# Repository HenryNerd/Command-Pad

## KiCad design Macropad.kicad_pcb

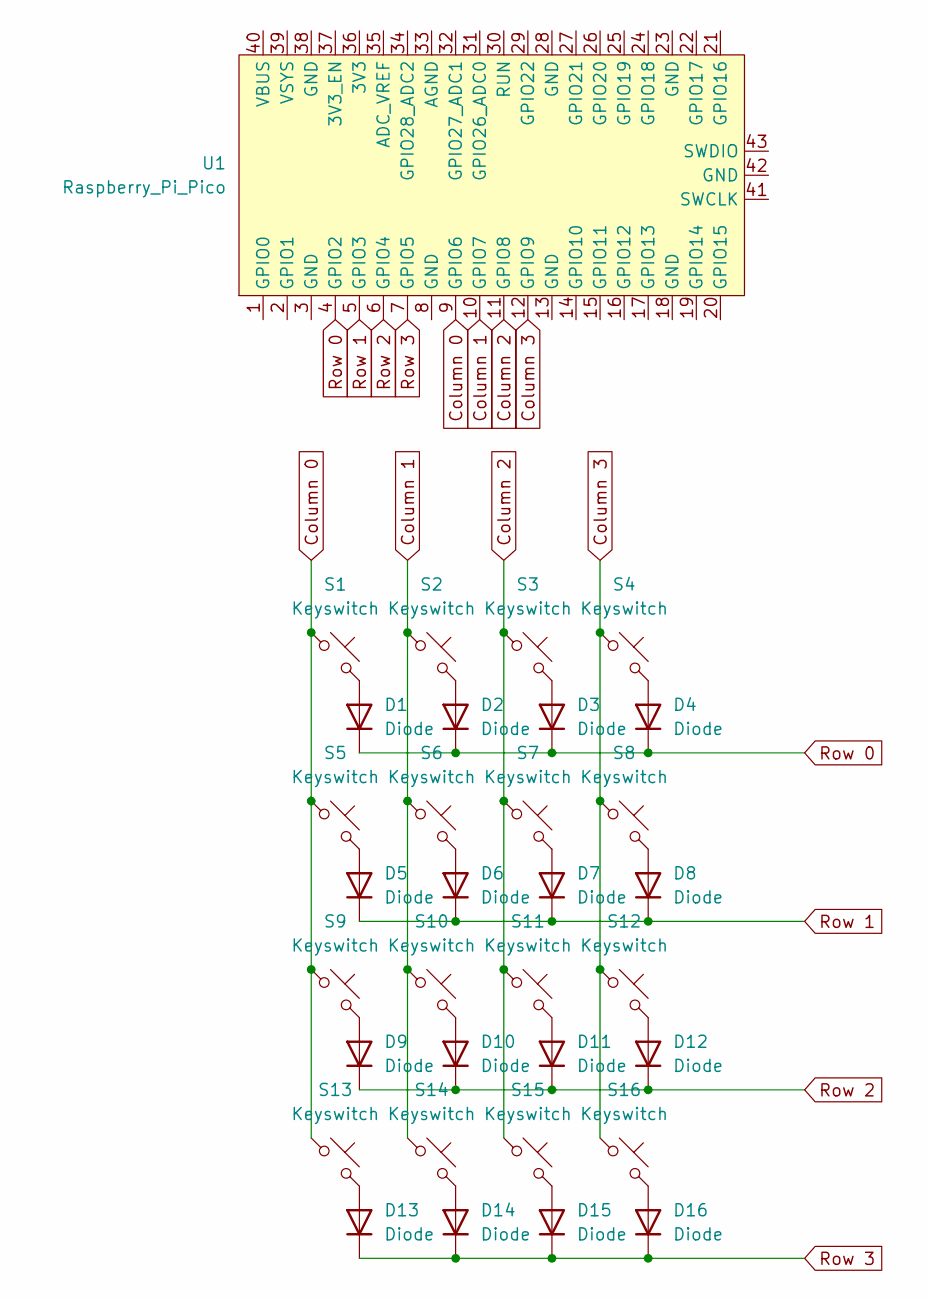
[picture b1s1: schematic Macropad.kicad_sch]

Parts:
D1, D2, D3, D4, D5, D6, D7, D8, D9, D10, D11, D12, D13, D14, D15, D16: Diode
S1, S2, S3, S4, S5, S6, S7, S8, S9, S10, S11, S12, S13, S14, S15, S16: Keyswitch
U1: Raspberry_Pi_Pico

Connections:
Column 0: S1.1, S5.1, S9.1, S13.1, U1.9 (GPIO6)
Column 1: S2.1, S6.1, S10.1, S14.1, U1.10 (GPIO7)
Column 2: S3.1, S7.1, S11.1, S15.1, U1.11 (GPIO8)
Column 3: S4.1, S8.1, S12.1, S16.1, U1.12 (GPIO9)
unnamed: D1.2 (A), S1.2
unnamed: D2.2 (A), S2.2
unnamed: D3.2 (A), S3.2
unnamed: D4.2 (A), S4.2
unnamed: D5.2 (A), S5.2
unnamed: D6.2 (A), S6.2
unnamed: D7.2 (A), S7.2
unnamed: D8.2 (A), S8.2
unnamed: D9.2 (A), S9.2
unnamed: D10.2 (A), S10.2
unnamed: D11.2 (A), S11.2
unnamed: D12.2 (A), S12.2
unnamed: D13.2 (A), S13.2
unnamed: D14.2 (A), S14.2
unnamed: D15.2 (A), S15.2
unnamed: D16.2 (A), S16.2
Row 0: D1.1 (K), D2.1 (K), D3.1 (K), D4.1 (K), U1.4 (GPIO2)
Row 1: D5.1 (K), D6.1 (K), D7.1 (K), D8.1 (K), U1.5 (GPIO3)
Row 2: D9.1 (K), D10.1 (K), D11.1 (K), D12.1 (K), U1.6 (GPIO4)
Row 3: D13.1 (K), D14.1 (K), D15.1 (K), D16.1 (K), U1.7 (GPIO5)

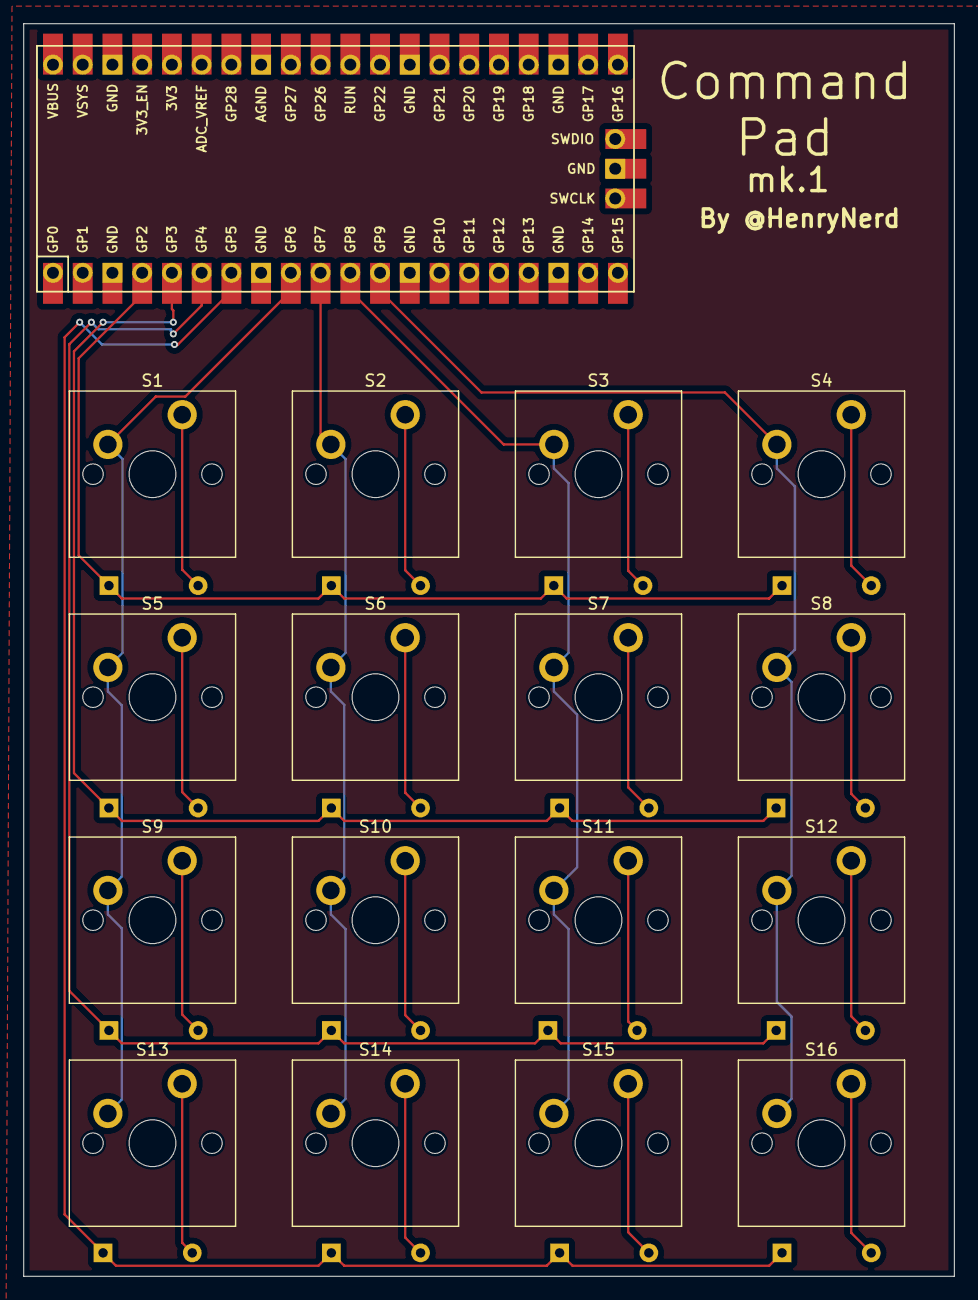
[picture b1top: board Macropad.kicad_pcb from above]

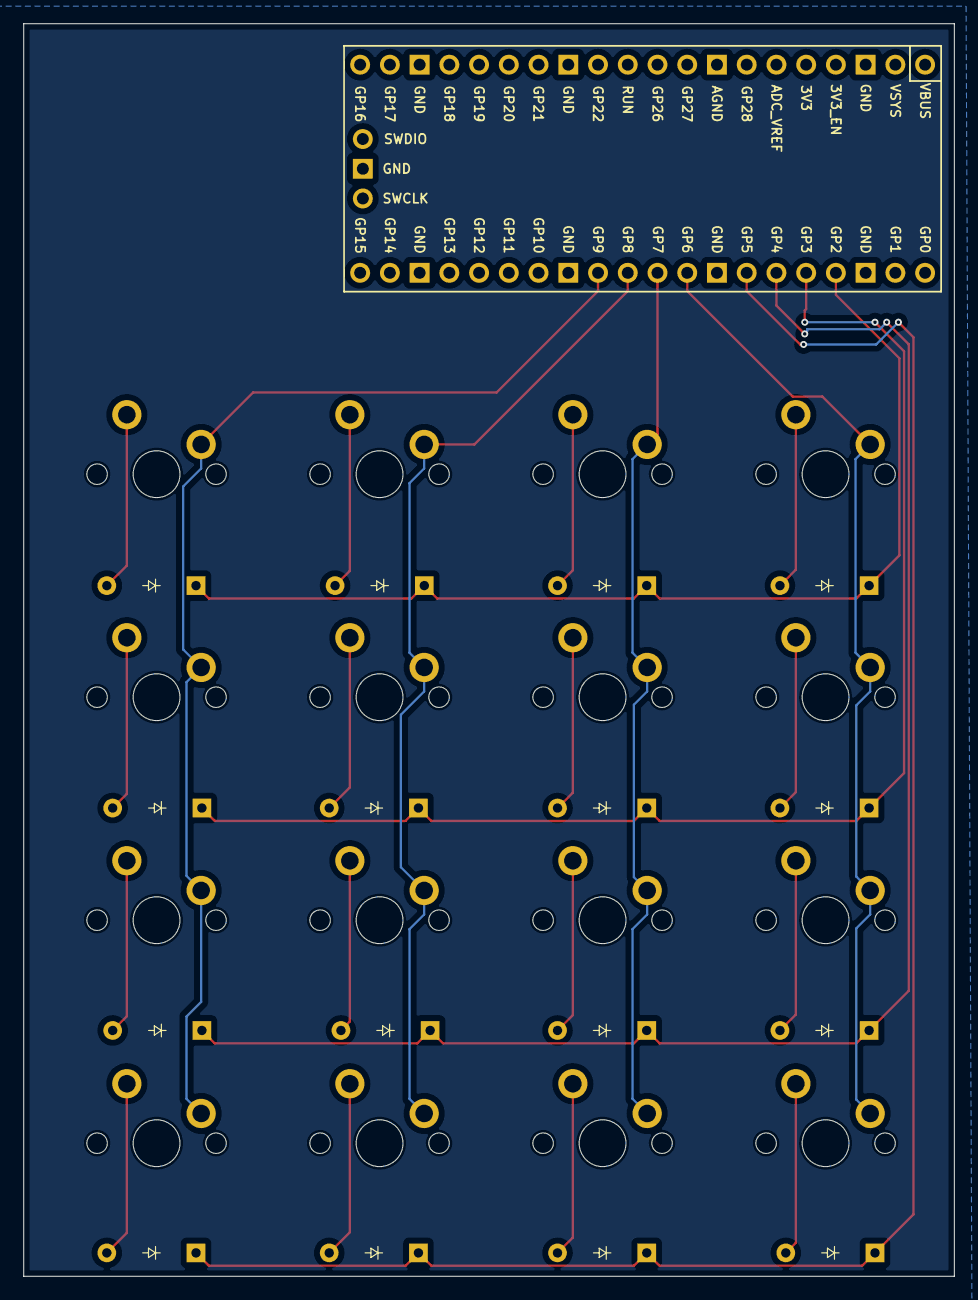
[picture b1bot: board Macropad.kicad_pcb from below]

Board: 2 copper layers, 79.5 x 107.0 mm, 33 parts (16 on the bottom side), 24 nets.

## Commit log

2024-07-28 Add Schematic
